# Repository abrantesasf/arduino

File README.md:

# Arduino

Repositório para estudo e testes com a plataforma Arduino e
microcontroladores Atmel AVR.

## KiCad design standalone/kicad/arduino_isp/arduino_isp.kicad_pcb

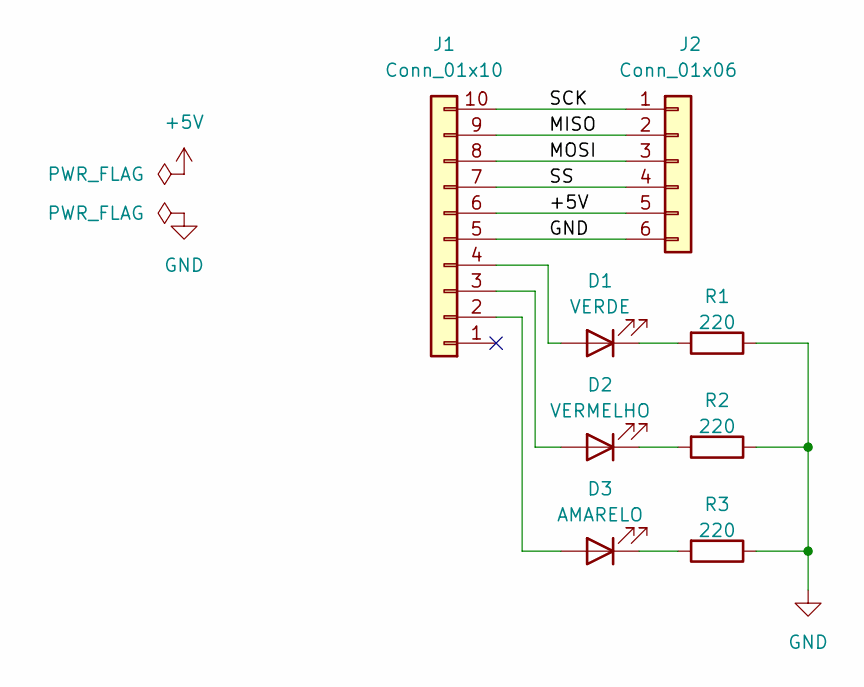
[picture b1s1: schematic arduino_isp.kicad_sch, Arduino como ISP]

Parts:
D1: VERDE; LED_D5.0mm
D2: VERMELHO; LED_D5.0mm
D3: AMARELO; LED_D5.0mm
J1: Conn_01x10; PinSocket_1x10_P2.54mm_Vertical
J2: Conn_01x06; PinSocket_1x06_P2.54mm_Vertical
R1, R2, R3: 220; R_Axial_DIN0207_L6.3mm_D2.5mm_P10.16mm_Horizontal

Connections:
+5V: J1.6, J2.5
/MISO: J1.9, J2.2
/MOSI: J1.8, J2.3
/SCK: J1.10, J2.1
/SS: J1.7, J2.4
GND: J1.5, J2.6, R1.1, R2.1, R3.1
unnamed: D1.2 (A), J1.4
unnamed: D1.1 (K), R1.2
unnamed: D2.2 (A), J1.3
unnamed: D2.1 (K), R2.2
unnamed: D3.2 (A), J1.2
unnamed: D3.1 (K), R3.2

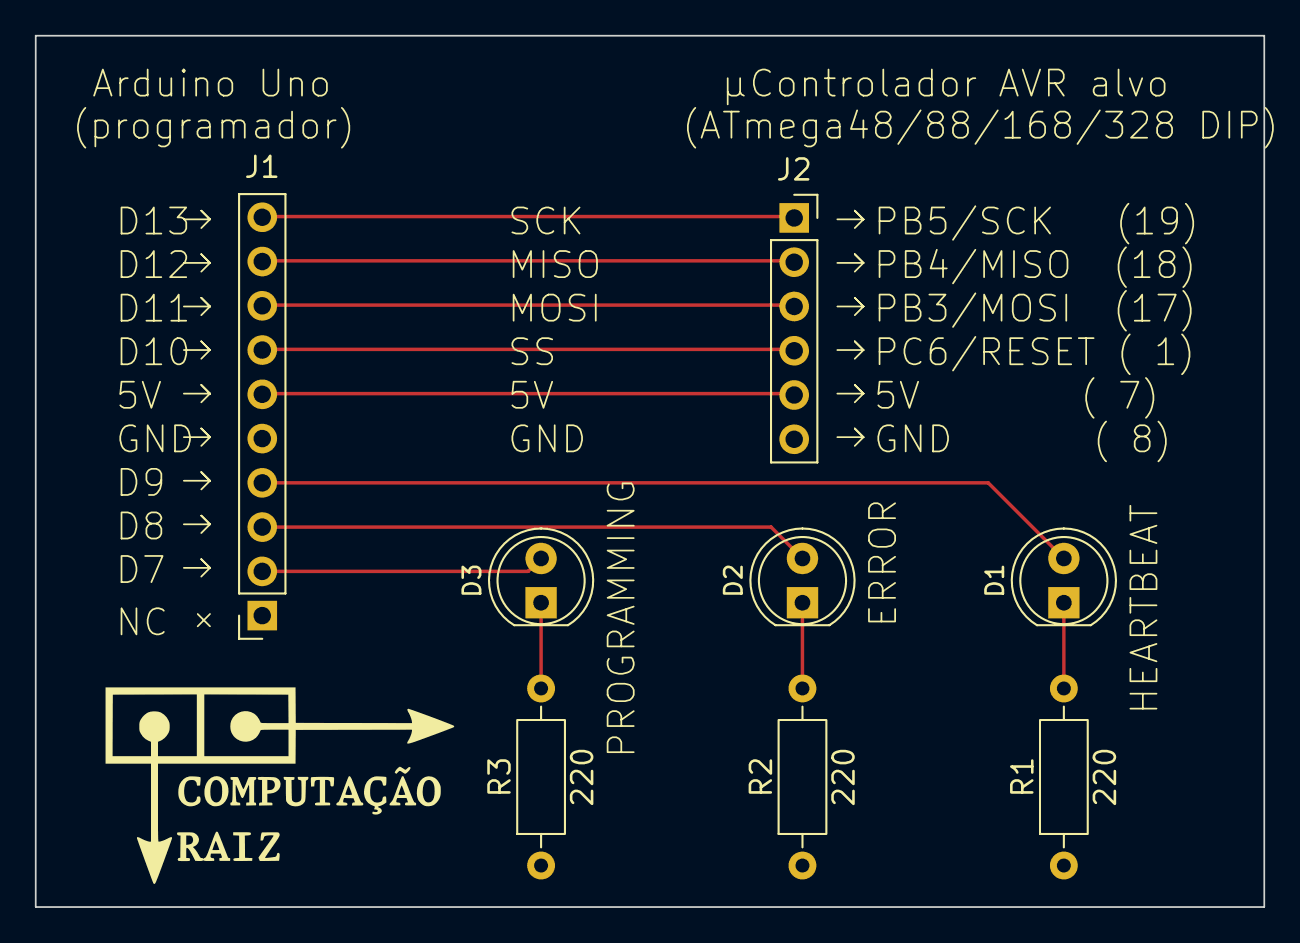
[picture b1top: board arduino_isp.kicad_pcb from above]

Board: 2 copper layers, 70.5 x 50.0 mm, 8 parts (0 on the bottom side), 12 nets.

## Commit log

2018-05-27 Exercícios do capitulo 2.
2025-11-18 Removendo diretórios antigos
2025-11-18 Fiat Lux (novamente)
2025-11-18 Início da intro
2025-11-18 Início dos materiais
2025-11-19 Continuar seção materiais (falta circuito de reset)
2025-11-19 Finalização da seção de materiais
2025-11-21 Finalizada montagem da alimentação
2025-11-21 Início do esquemático do ATmega328P
2025-11-22 Finalização versão em português
2025-11-24 KiCAD
2025-11-25 PCB do Arduino ISP
2025-11-25 Atualizações na placa
2025-11-26 Troca do conector de 9 para 10 pinos
2025-11-27 Ajustes no Silkscreen
2025-11-28 Finalização da placa Aruino ISP
2026-01-19 Datasheets; mapa
2026-01-21 Inclusão da discussão sobre ânodo e cátodo em baterias
